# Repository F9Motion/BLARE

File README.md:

# BLARE
BLARE - is cutom alarm clock. Of course, you can use your phone but, come on! Custom alarm clock more interesting than phone. This is cube form alarm clock with display and 4 buttons.

# Why I made this?
I find this project in FABRICATE tutorials and find this **BLARE**. I haven't any other alarm clock so this good thing for me.

# Feautures
1. This alarm clock have a display(or had if you like me just steal things from old projects to make new project :D)
2. Have 4 buttons (or had) if you think 2 is a few
3. Case printed in 3D printer if you haven't 3D printer you can use service printing legion from hack club
4. This alarm clock is with firmware writed in Arduino IDE

# Imagines

# How it works?
The firmware is in **ESP32**, so you can use Arduino IDE for writing firmware and the best function of this is... this is custom! That means you can upload to ESP32 not mine, your firmware if you want. So it's works: 4 buttons put signal to ESP32 "we pushshed!" and ESP32 "OK".

# How to assemble
Just to this step and use Blade:
1. Print the **PCB** from JLCPCB
2. Order microcontrollers(you can find this in BOM)
3. Solder to PCB this microcontrollers
4. Print CAD in 3D printer
5. Instal firmware to ESP32
6. Use this!

# Bill Of Materials(BOM)
| Name         | Price | Link |
|--------------|-------|------|
| XIAO ESP32   | $4.9  | https://www.seeedstudio.com/Seeed-XIAO-ESP32C3-p-5431.html |
| switchs      | $7.42 | https://aliexpress.ru/item/4001111706889.html?shpMethod=CAINIAO_STANDARD&sku_id=10000014442813977&spm=a2g2w.productlist.search_results.0.48c575ddYCQpmf         |
| Buzzer       | $1.25 | https://aliexpress.ru/item/1005006613648485.html?shpMethod=AE_CN_SUPER_ECONOMY_G&sku_id=12000037825538791&spm=a2g2w.productlist.search_results.0.17d02d3dQT85Dr |
| Display      | $4.02 | https://aliexpress.ru/item/1005012250582857.html?shpMethod=AE_CN_SUPER_ECONOMY_G&sku_id=12000057857651313&spm=a2g2w.productlist.search_results.5.4d2f7214h6M6bk |
| wire         | $1.5  | https://aliexpress.ru/item/1005004338950885.html?shpMethod=AE_CN_SUPER_ECONOMY_G&sku_id=12000028815659129&spm=a2g2w.productlist.search_results.4.4d0d4feaKCfQsK |
| Printing PCB | $9    | JLCPCB no link |
| bottom.step  | $0.4  | felament price only |
| top.step     | $0.09 | felament price only |

# Credits
Blender, KiCad, Arduino
Worked person: Rasul

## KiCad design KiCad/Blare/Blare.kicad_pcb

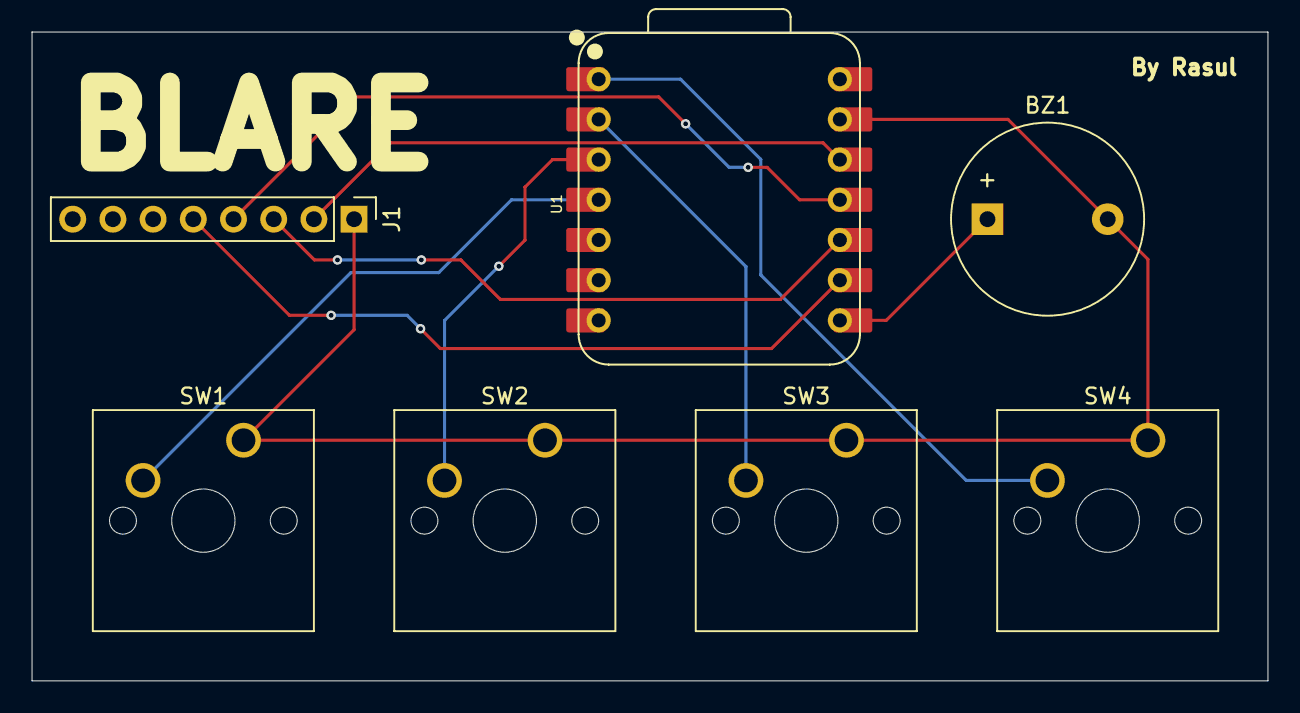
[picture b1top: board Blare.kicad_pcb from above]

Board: 2 copper layers, 78.1 x 41.0 mm, 7 parts (0 on the bottom side), 10 nets.

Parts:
BZ1: Buzzer; Buzzer_12x9.5RM7.6
J1: Conn_01x08_Pin; PinHeader_1x08_P2.54mm_Vertical
SW1, SW2, SW3, SW4: SW_Push; SW_Cherry_MX_1.00u_PCB
U1: XIAO-ESP32-C3-SMD; XIAO-ESP32-C3-DIP

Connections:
+3.3V: J1.2, U1.12 (3V3_OUT)
GND: BZ1.2 (-), J1.1, SW1.1, SW2.1, SW3.1, SW4.1, U1.13 (GND)
unnamed: BZ1.1 (+), U1.8 (D7)
unnamed: J1.3, U1.10 (D9/BOOT)
unnamed: J1.4, U1.11 (D10)
unnamed: J1.5, U1.9 (D8)
unnamed: SW4.2, U1.1 (D0)
unnamed: SW3.2, U1.2 (D1)
unnamed: SW2.2, U1.3 (D2)
unnamed: SW1.2, U1.4 (D3)
